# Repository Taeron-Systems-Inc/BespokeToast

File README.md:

# BespokeToast

Firmware for a toaster oven converted to a reflow soldering oven, controlled
by an Adafruit PyPortal.

This repository holds the current state of the oven: the firmware running on
it today, the measurements that firmware is built from, the runs that back
the numbers, and reference notes on the hardware it drives.

## What you need

| | |
|---|---|
| The oven | a PyPortal wired to a mains relay and an MCP9601 thermocouple amplifier (Adafruit 5165) and a type-K probe (Adafruit 3245) — `docs/hardware.md` describes the one this was built for |
| A host | anything running Python 3 that can mount USB mass storage and open a serial port. A Raspberry Pi is enough |
| A build host | only to change anything under `firmware/oven/`: ~3 GB of disk and an ARM toolchain. It does not have to be the machine attached to the oven |

## Putting the firmware on a board for the first time

The oven's own package is **frozen into the CircuitPython image**, so an
install is two halves: an image to flash, and a set of files to copy.

**1. Get an image.** Either build one — `docs/frozen-build.md` has the
toolchain, the source version and the one patch that is required — or use
an image that was built and tested earlier, if you have one. Images are not
in this repository: a `.uf2` is a build artefact, and the one that matters
is always paired with a `code.py`, which is not frozen and does not travel
inside it. Keep the pair together.

**2. Flash it.** The board must be in its UF2 bootloader, which shows up as
a volume named `PORTALBOOT`. On a board already running this firmware, ask
for it over the serial console:

```python
import microcontroller
microcontroller.on_next_reset(microcontroller.RunMode.BOOTLOADER)
microcontroller.reset()
```

On a board that will not boot, or has never run this, double-tap the reset
button instead — which on this oven means opening the panel. Copy the
`.uf2` onto `PORTALBOOT`; the board reboots itself and comes back as
`CIRCUITPY`.

**3. Copy the files that are not frozen.** Mount the volume writable and
deploy:

```
sudo mount -o rw,uid=$(id -u) /dev/disk/by-label/CIRCUITPY /mnt/circuitpy
python3 tools/deploy.py /mnt/circuitpy --dry-run    # what it would write
python3 tools/deploy.py /mnt/circuitpy
```

That copies `boot.py`, `code.py`, `settings.toml`, `profiles/` and
`assets/`, plus `data/oven-characterisation.json` as `characterisation.json`,
then verifies every file by digest. It skips `oven/` when it sees the board
is running a frozen build, refuses to run while a profile is running, and
refuses if the Adafruit libraries have reappeared on the volume — a copy
there shadows the frozen one and silently costs about 20 kB of RAM.

**4. Give it the network, if you want the web page.** Copy
`wifi.json.example` to `wifi.json` **on the volume** — not into this
repository — and fill in the SSIDs and passwords:

```
cp wifi.json.example /mnt/circuitpy/wifi.json
$EDITOR /mnt/circuitpy/wifi.json
```

The oven scans and joins whichever listed network it hears most strongly.
Without the file it runs perfectly well, with logs stamped from boot
instead of wall clock and no page. `wifi.json` is in `.gitignore`, deploy
never writes it, and anyone who can plug a cable into the board can read
it — `docs/network.md` covers that and the rest.

The template also carries two worked examples, switched off behind
underscored keys: a network entry with a **fixed address** (`ip` and
`gateway`, required together), and an **archive** block that POSTs each
finished run to a receiver — `tools/collector/serve.py` is one. Neither is
needed to use the oven.

**5. Hand the volume back to the oven.**

```
sudo umount /mnt/circuitpy
python3 tools/deploy.py --standalone
```

A deploy needs the **host** to own `CIRCUITPY`; the oven needs to own it to
record a run. Only one direction is automatic, so an oven left in host mode
runs perfectly and keeps no record of it. The power-on screen says which
mode it is in, next to *run logging*.

**6. Check it came up.** The splash and self-test panel, then the home
screen within about 15 seconds; the network line fills in behind it. Press
nothing until the home screen shows a temperature that looks like the room.

## Getting changes onto an oven that already runs it

Which path you need depends on the file:

| Changed | How it ships |
|---|---|
| `code.py`, `profiles/`, `assets/`, `characterisation.json` | `tools/deploy.py`, as above |
| anything under `firmware/oven/` | rebuild and reflash |

```
export TOASTER_BUILD_HOST=user@host    # the machine with the toolchain
python3 tools/release.py --check       # what would happen, touching nothing
python3 tools/release.py --flash       # build, flash, verify
python3 tools/release.py --rollback    # the image before the last one
```

Writing to `CIRCUITPY` triggers CircuitPython's auto-reload, which restarts
the controller immediately. Never deploy while a profile is running; deploy
refuses unless forced.

## Testing

```
python3 -m pytest tests/
python3 tools/score_runs.py      # recompute the figures the docs quote
```

Everything runs on a laptop. That is deliberate and enforced: a test parses
every module in `oven/` and fails if anything other than `hardware.py`
imports `board`. The previous firmware became untestable one import at a
time. `code.py` is never imported by the suite — it needs a board — so it
is checked by parsing instead.

`tools/onboard_test.py` is the other half: it drives the new code on a real
board from the REPL without replacing what the board boots, which is the
right first step on a board that has never run this firmware.

## Safety

This switches 120 VAC into a heating element.

The relay fails safe: `D4` has an external pulldown, so the relay is
de-energised whenever the pin is not driven — which includes every reset,
every Ctrl-C and every auto-reload. A supervisor independent of the control
loop holds a 260 C ceiling, an enclosure limit, rate and stall guards, and
ABORT is always available. The web page cannot start or abort a run, and a
test walks the routes to keep it that way.

Read `docs/hardware.md` before working on the oven, and
`docs/control-loop.md` before changing how it heats. Every run behind the
numbers in those documents was made with an **empty oven**.

## Layout

```
firmware/    What ships to the device.
  code.py    Entry point: screens, console, web service, wiring.
  oven/      Control, safety, profiles, metrics, interface. Only
             hardware.py touches the board; everything else is plain
             stdlib and runs under CPython.
  profiles/  Reflow and bake profiles as JSON.
  assets/    Fonts and logo.
tests/       pytest, off-hardware. Includes a simulated oven built from
             this oven's own measured response.
tools/       Host-side: deploy, release and rollback, profile generation,
             plant identification, run scoring, screen rendering.
  device/    Runs on the board over the serial console.
  host/      Runs on the bench machine.
  collector/ Receives finished runs.
  design/    Simulation harnesses used to choose the control loop.
data/        Measured characterisation, step tests, and the runs the
             documentation cites. See data/README.md.
docs/        Hardware, network, control loop, profiles, build, validation.
```

## Documentation

| | |
|---|---|
| `docs/hardware.md` | the oven, the controller, what is measured and what is assumed |
| `docs/control-loop.md` | how it heats, what it achieves, and the rules a replacement must keep |
| `docs/profiles.md` | each paste's profile and why its numbers are what they are |
| `docs/network.md` | credentials, the web page, what the radio costs |
| `docs/frozen-build.md` | building, flashing, rolling back, who owns the volume |
| `docs/on-device-validation.md` | what has actually been run |
| `data/README.md` | which runs are in the repository, and how to fetch one that is not |

## Tags

| | |
|---|---|
| `v1` | the oven's state as found, before the rewrite |
| `v2.0` | this firmware: pre-charge, predictive tracking, supervisor, run logging. The firmware reports the same name on the splash and in every run log header |

A tag records the source. The image and `code.py` that were tested together
are kept outside the repository, because a `.uf2` is a build artefact; see
*Rolling back* in `docs/control-loop.md`.

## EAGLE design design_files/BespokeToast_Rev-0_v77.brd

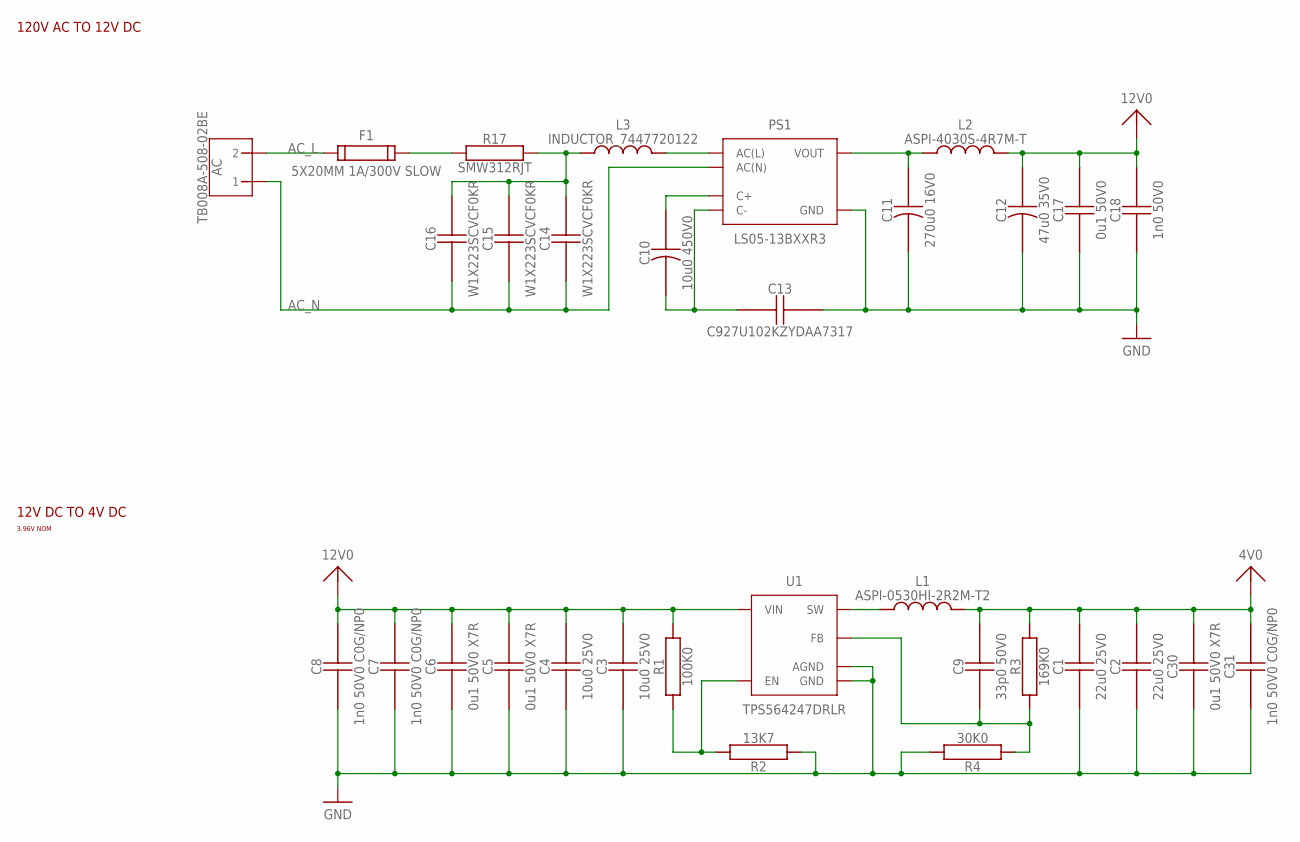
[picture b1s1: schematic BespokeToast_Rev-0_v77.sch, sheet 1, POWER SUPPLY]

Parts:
AC: TB008A-508-02BE
C1, C2: 22u0 25V0; SAMSUNG_CAP-0805
C3, C4: 10u0 25V0; SAMSUNG_CAP-0805
C5, C6, C30: 0u1 50V0 X7R; SAMSUNG_CAP-0402
C7, C8, C31: 1n0 50V0 C0G/NP0; SAMSUNG_CAP-0402
C9: 33p0 50V0; SAMSUNG_CAP-0402
C10: 10u0 450V0; RUBYCON_CAP-POL-5X10
C11: 270u0 16V0; RUBYCON_CAP-POL-3.5X8
C12: 47u0 35V0; RUBYCON_CAP-POL-3.5X8
C13: C927U102KZYDAA7317; TH_CAP-7.5
C14, C15, C16: W1X223SCVCF0KR; TH_CAP-7.5
C17: 0u1 50V0; SAMSUNG_CAP-0402
C18: 1n0 50V0; SAMSUNG_CAP-0402
F1: 5X20MM 1A/300V SLOW; FC-203-22
L1: ASPI-0530HI-2R2M-T2
L2: ASPI-4030S-4R7M-T
L3: INDUCTOR_7447720122; 7447720122
PS1: LS05-13BXXR3
R1: 100K0; YAGEO_RES-0402
R2: 13K7; YAGEO_RES-0402
R3: 169K0; YAGEO_RES-0402
R4: 30K0; YAGEO_RES-0402
R17: SMW312RJT
U1: TPS564247DRLR

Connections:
4V0: C1.P$2, C2.P$2, C9.P$2, C30.P$2, C31.P$2, L1.P$2, R3.P$2; also elsewhere on the board
12V0: C3.P$2, C4.P$2, C5.P$2, C6.P$2, C7.P$2, C8.P$2, C12.+, C17.P$2, C18.P$2, L2.P$2, R1.P$2, U1.P$1 (VIN); also elsewhere on the board
AC_L: AC.P$2 (2), F1.P$1, F1.P$2; also elsewhere on the board
AC_N: AC.P$1 (1), C14.P$1, C15.P$1, C16.P$1, PS1.P$2 (AC(N)); also elsewhere on the board
GND: C1.P$1, C2.P$1, C3.P$1, C4.P$1, C5.P$1, C6.P$1, C7.P$1, C8.P$1, C11.-, C12.-, C13.P$2, C17.P$1, C18.P$1, C30.P$1, C31.P$1, PS1.P$5 (GND), R2.P$1, R4.P$2, U1.P$3 (GND), U1.P$4 (AGND); also elsewhere on the board
unnamed: R1.P$1, R2.P$2, U1.P$5 (EN)
unnamed: C10.+, PS1.P$3 (C+)
unnamed: C10.-, C13.P$1, PS1.P$4 (C-)
unnamed: C11.+, L2.P$1, PS1.P$6 (VOUT)
unnamed: F1.P$3, F1.P$4, R17.P$2
unnamed: C9.P$1, R3.P$1, R4.P$1, U1.P$6 (FB)
unnamed: C14.P$2, C15.P$2, C16.P$2, L3.P$1, R17.P$1
unnamed: L3.P$2, PS1.P$1 (AC(L))
OUT: L1.P$1, U1.P$2 (SW)

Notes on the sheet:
120V AC TO 12V DC
12V DC TO 4V DC
3.96V NOM

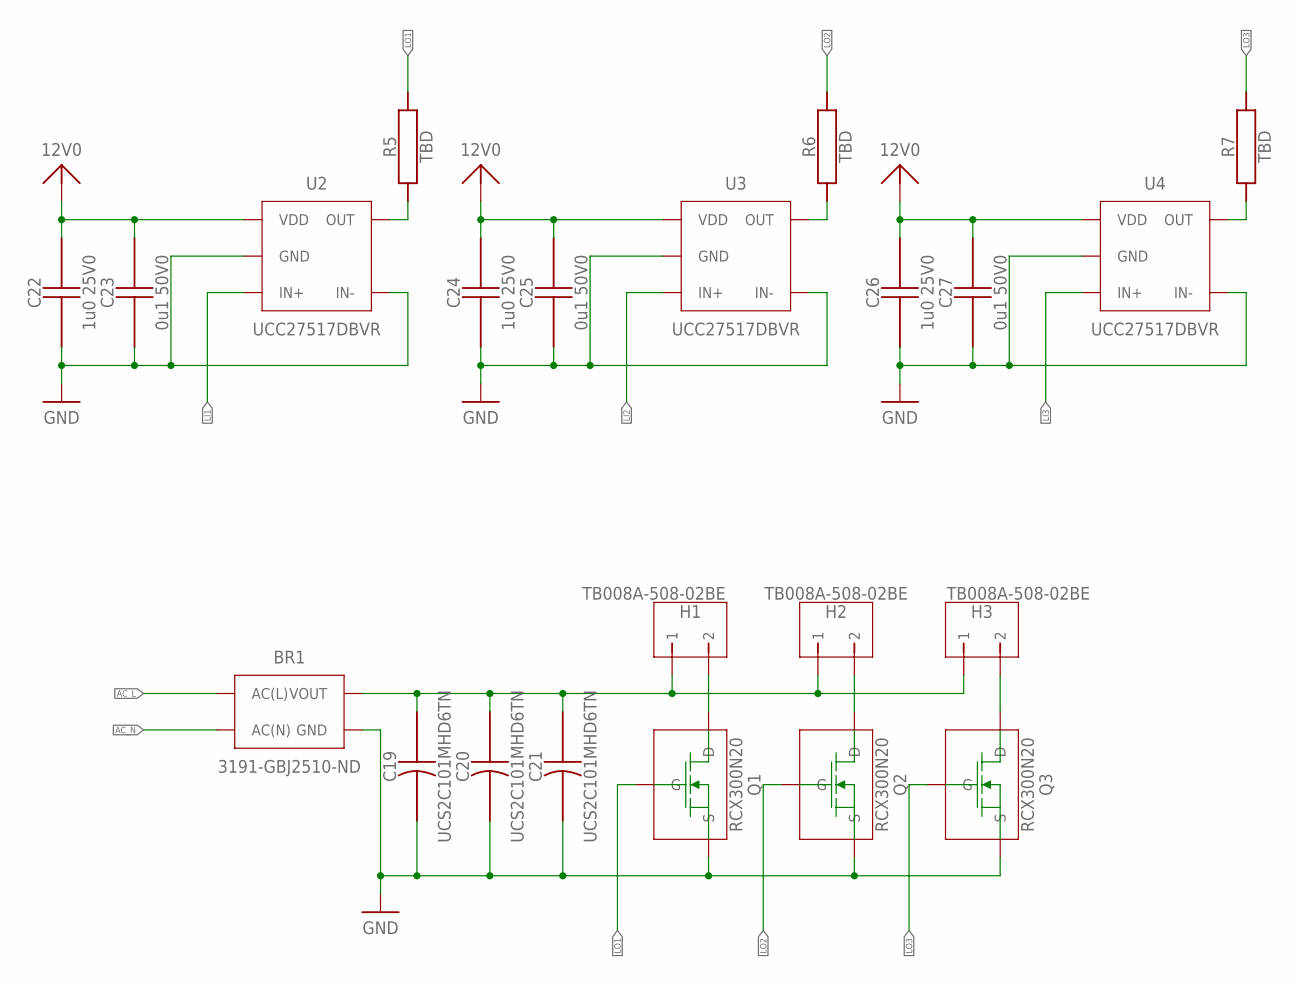
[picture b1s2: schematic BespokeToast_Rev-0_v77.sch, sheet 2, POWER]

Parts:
BR1: 3191-GBJ2510-ND; GBJ2510
C19, C20, C21: UCS2C101MHD6TN; RUBYCON_CAP-POL-7.5X16
C22, C24, C26: 1u0 25V0; SAMSUNG_CAP-0805
C23, C25, C27: 0u1 50V0; SAMSUNG_CAP-0402
H1, H2, H3: TB008A-508-02BE
Q1, Q2, Q3: RCX300N20; FET_TO220-VTH
R5, R6, R7: TBD; YAGEO_RES-0402
U2, U3, U4: UCC27517DBVR

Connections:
12V0: C22.P$2, C23.P$2, C24.P$2, C25.P$2, C26.P$2, C27.P$2, U2.P$1 (VDD), U3.P$1 (VDD), U4.P$1 (VDD); also elsewhere on the board
AC_L: BR1.P$2 (AC(L)); also elsewhere on the board
AC_N: BR1.P$3 (AC(N)); also elsewhere on the board
GND: BR1.P$4 (GND), C19.-, C20.-, C21.-, C22.P$1, C23.P$1, C24.P$1, C25.P$1, C26.P$1, C27.P$1, Q1.S, Q2.S, Q3.S, U2.P$2 (GND), U2.P$4 (IN-), U3.P$2 (GND), U3.P$4 (IN-), U4.P$2 (GND), U4.P$4 (IN-); also elsewhere on the board
LI1: U2.P$3 (IN+); also elsewhere on the board
LI2: U3.P$3 (IN+); also elsewhere on the board
LI3: U4.P$3 (IN+); also elsewhere on the board
LO1: Q1.G, R5.P$2
LO2: Q2.G, R6.P$2
LO3: Q3.G, R7.P$2
unnamed: H1.P$2 (2), Q1.D
unnamed: H2.P$2 (2), Q2.D
unnamed: H3.P$2 (2), Q3.D
unnamed: BR1.P$1 (VOUT), C19.+, C20.+, C21.+, H1.P$1 (1), H2.P$1 (1), H3.P$1 (1)
unnamed: R6.P$1, U3.P$5 (OUT)
unnamed: R5.P$1, U2.P$5 (OUT)
unnamed: R7.P$1, U4.P$5 (OUT)

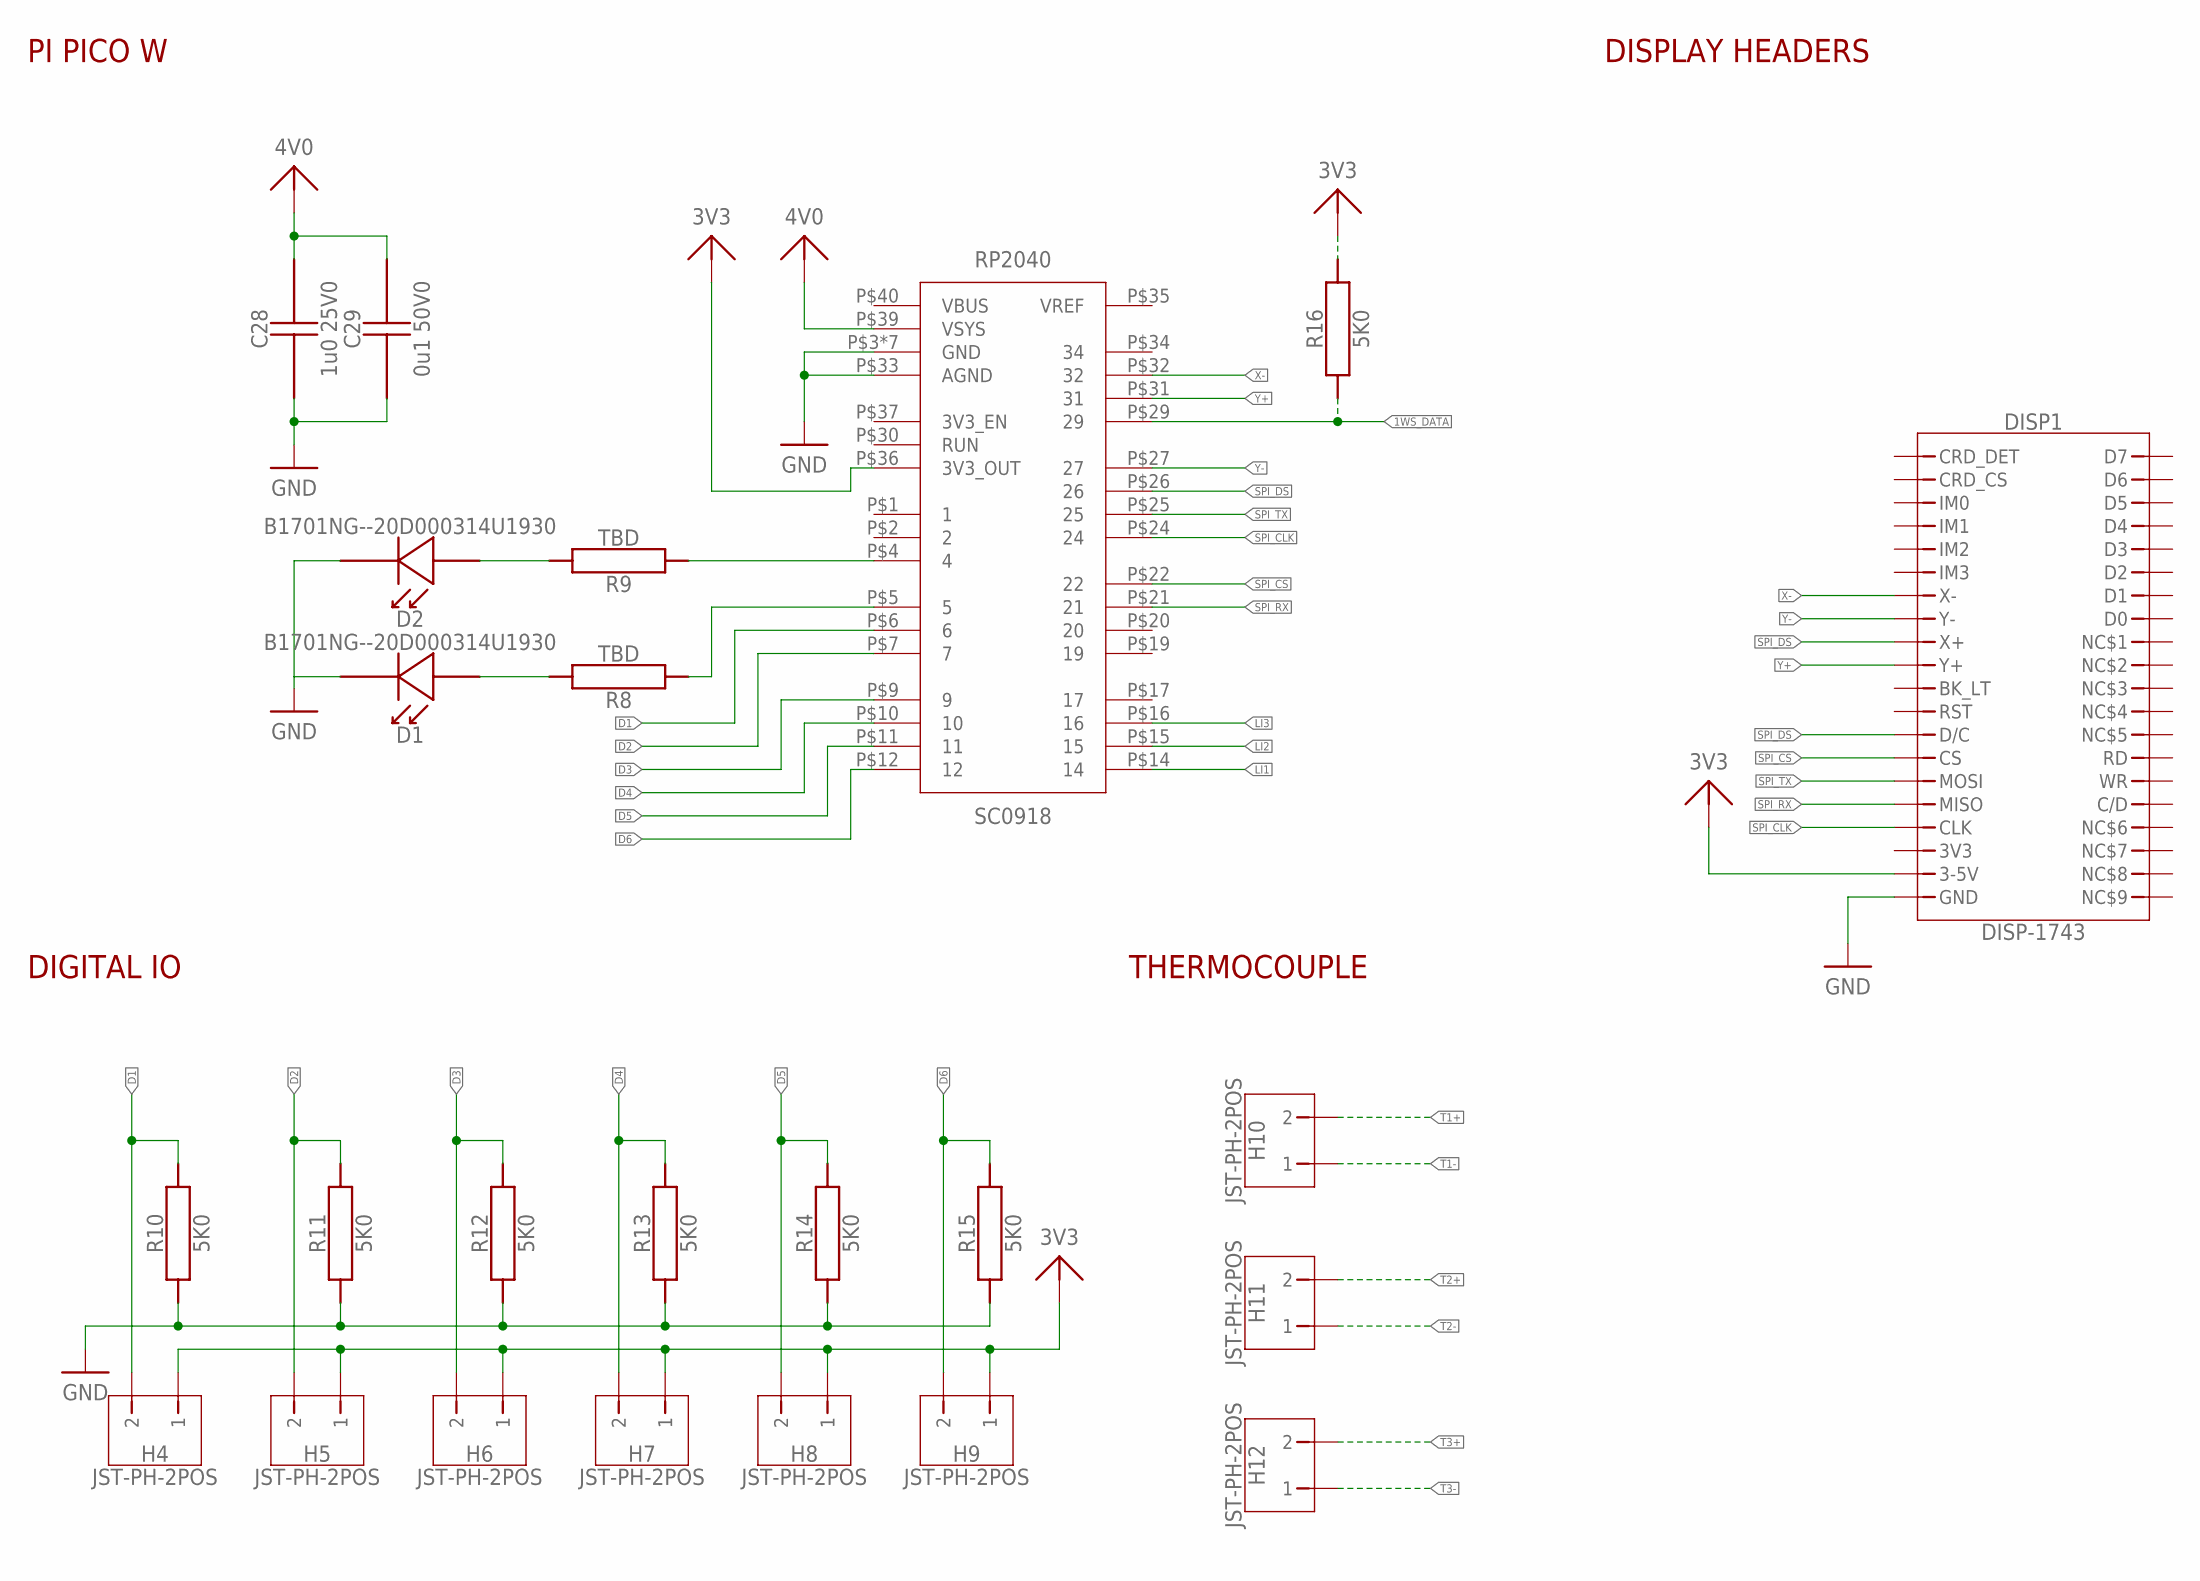
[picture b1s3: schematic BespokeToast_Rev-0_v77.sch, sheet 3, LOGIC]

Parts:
C28: 1u0 25V0; SAMSUNG_CAP-0805
C29: 0u1 50V0; SAMSUNG_CAP-0402
D1, D2: B1701NG--20D000314U1930
DISP1: DISP-1743
H4, H5, H6, H7, H8, H9, H10, H11, H12: JST-PH-2POS
R8, R9: TBD; YAGEO_RES-0402
R10, R11, R12, R13, R14, R15, R16: 5K0; YAGEO_RES-0402
RP2040: SC0918; SC0915

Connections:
1WS_DATA: R16.P$1, RP2040.P$29 (29); also elsewhere on the board
3V3: DISP1.P$19 (3-5V), H4.P$1 (1), H5.P$1 (1), H6.P$1 (1), H7.P$1 (1), H8.P$1 (1), H9.P$1 (1), R16.P$2, RP2040.P$36 (3V3_OUT)
4V0: C28.P$2, C29.P$2, RP2040.P$39 (VSYS); also elsewhere on the board
D1: H4.P$2 (2), R10.P$2, RP2040.P$6 (6)
D2: H5.P$2 (2), R11.P$2, RP2040.P$7 (7)
D3: H6.P$2 (2), R12.P$2, RP2040.P$9 (9)
D4: H7.P$2 (2), R13.P$2, RP2040.P$10 (10)
D5: H8.P$2 (2), R14.P$2, RP2040.P$11 (11)
D6: H9.P$2 (2), R15.P$2, RP2040.P$12 (12)
GND: C28.P$1, C29.P$1, D1.P$1 (VSS), D2.P$1 (VSS), DISP1.P$20 (GND), R10.P$1, R11.P$1, R12.P$1, R13.P$1, R14.P$1, R15.P$1, RP2040.P$3 (GND), RP2040.P$8 (GND), RP2040.P$13 (GND), RP2040.P$18 (GND), RP2040.P$23 (GND), RP2040.P$28 (GND), RP2040.P$33 (AGND), RP2040.P$38 (GND); also elsewhere on the board
LI1: RP2040.P$14 (14); also elsewhere on the board
LI2: RP2040.P$15 (15); also elsewhere on the board
LI3: RP2040.P$16 (16); also elsewhere on the board
unnamed: D1.P$2 (VDD), R8.P$2
unnamed: D2.P$2 (VDD), R9.P$2
unnamed: R8.P$1, RP2040.P$5 (5)
unnamed: R9.P$1, RP2040.P$4 (4)
SPI_CLK: DISP1.P$17 (CLK), RP2040.P$24 (24)
SPI_CS: DISP1.P$14 (CS), RP2040.P$22 (22)
SPI_DS: DISP1.P$9 (X+), DISP1.P$13 (D/C), RP2040.P$26 (26)
SPI_RX: DISP1.P$16 (MISO), RP2040.P$21 (21)
SPI_TX: DISP1.P$15 (MOSI), RP2040.P$25 (25)
T1+: H10.P$2 (2); also elsewhere on the board
T1-: H10.P$1 (1); also elsewhere on the board
T2+: H11.P$2 (2); also elsewhere on the board
T2-: H11.P$1 (1); also elsewhere on the board
T3+: H12.P$2 (2); also elsewhere on the board
T3-: H12.P$1 (1); also elsewhere on the board
X-: DISP1.P$7 (X-), RP2040.P$32 (32)
Y+: DISP1.P$10 (Y+), RP2040.P$31 (31)
Y-: DISP1.P$8 (Y-), RP2040.P$27 (27)

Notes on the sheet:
DIGITAL IO
PI PICO W
DISPLAY HEADERS
THERMOCOUPLE

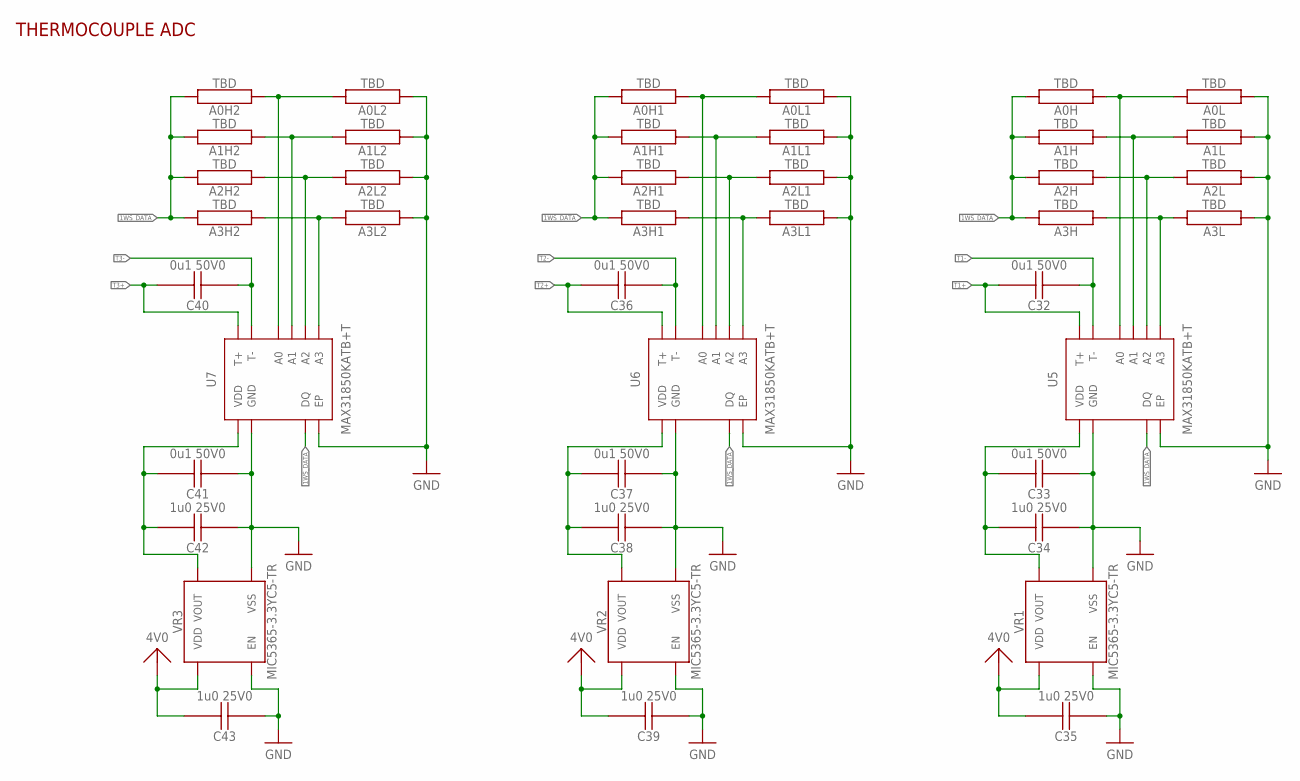
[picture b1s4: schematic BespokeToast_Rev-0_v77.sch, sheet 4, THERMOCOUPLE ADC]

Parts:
A0H, A0H1, A0H2, A0L, A0L1, A0L2, A1H, A1H1, A1H2, A1L, A1L1, A1L2, A2H, A2H1, A2H2, A2L, A2L1, A2L2, A3H, A3H1, A3H2, A3L, A3L1, A3L2: TBD; YAGEO_RES-0402
C32, C33, C36, C37, C40, C41: 0u1 50V0; SAMSUNG_CAP-0402
C34, C35, C38, C39, C42, C43: 1u0 25V0; SAMSUNG_CAP-0603
U5, U6, U7: MAX31850KATB+T; MAX31850
VR1, VR2, VR3: MIC5365-3.3YC5-TR

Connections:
1WS_DATA: A0H.P$2, A0H1.P$2, A0H2.P$2, A1H.P$2, A1H1.P$2, A1H2.P$2, A2H.P$2, A2H1.P$2, A2H2.P$2, A3H.P$2, A3H1.P$2, A3H2.P$2, U5.P$5 (DQ), U6.P$5 (DQ), U7.P$5 (DQ); also elsewhere on the board
4V0: C35.P$2, C39.P$2, C43.P$2, VR1.P$1 (VDD), VR2.P$1 (VDD), VR3.P$1 (VDD); also elsewhere on the board
GND: A0L.P$1, A0L1.P$1, A0L2.P$1, A1L.P$1, A1L1.P$1, A1L2.P$1, A2L.P$1, A2L1.P$1, A2L2.P$1, A3L.P$1, A3L1.P$1, A3L2.P$1, C33.P$1, C34.P$1, C35.P$1, C37.P$1, C38.P$1, C39.P$1, C41.P$1, C42.P$1, C43.P$1, U5.EP, U5.P$1 (GND), U6.EP, U6.P$1 (GND), U7.EP, U7.P$1 (GND), VR1.P$2 (VSS), VR1.P$3 (EN), VR2.P$2 (VSS), VR2.P$3 (EN), VR3.P$2 (VSS), VR3.P$3 (EN); also elsewhere on the board
unnamed: A0H.P$1, A0L.P$2, U5.P$6 (A0)
unnamed: A1H.P$1, A1L.P$2, U5.P$7 (A1)
unnamed: A2H.P$1, A2L.P$2, U5.P$8 (A2)
unnamed: A3H.P$1, A3L.P$2, U5.P$9 (A3)
unnamed: A0H1.P$1, A0L1.P$2, U6.P$6 (A0)
unnamed: A1H1.P$1, A1L1.P$2, U6.P$7 (A1)
unnamed: A2H1.P$1, A2L1.P$2, U6.P$8 (A2)
unnamed: A3H1.P$1, A3L1.P$2, U6.P$9 (A3)
unnamed: C33.P$2, C34.P$2, U5.P$4 (VDD), VR1.P$5 (VOUT)
unnamed: C37.P$2, C38.P$2, U6.P$4 (VDD), VR2.P$5 (VOUT)
unnamed: A0H2.P$1, A0L2.P$2, U7.P$6 (A0)
unnamed: A1H2.P$1, A1L2.P$2, U7.P$7 (A1)
unnamed: A2H2.P$1, A2L2.P$2, U7.P$8 (A2)
unnamed: A3H2.P$1, A3L2.P$2, U7.P$9 (A3)
unnamed: C41.P$2, C42.P$2, U7.P$4 (VDD), VR3.P$5 (VOUT)
T1+: C32.P$2, U5.P$3 (T+); also elsewhere on the board
T1-: C32.P$1, U5.P$2 (T-); also elsewhere on the board
T2+: C36.P$2, U6.P$3 (T+); also elsewhere on the board
T2-: C36.P$1, U6.P$2 (T-); also elsewhere on the board
T3+: C40.P$2, U7.P$3 (T+); also elsewhere on the board
T3-: C40.P$1, U7.P$2 (T-); also elsewhere on the board

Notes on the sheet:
THERMOCOUPLE ADC

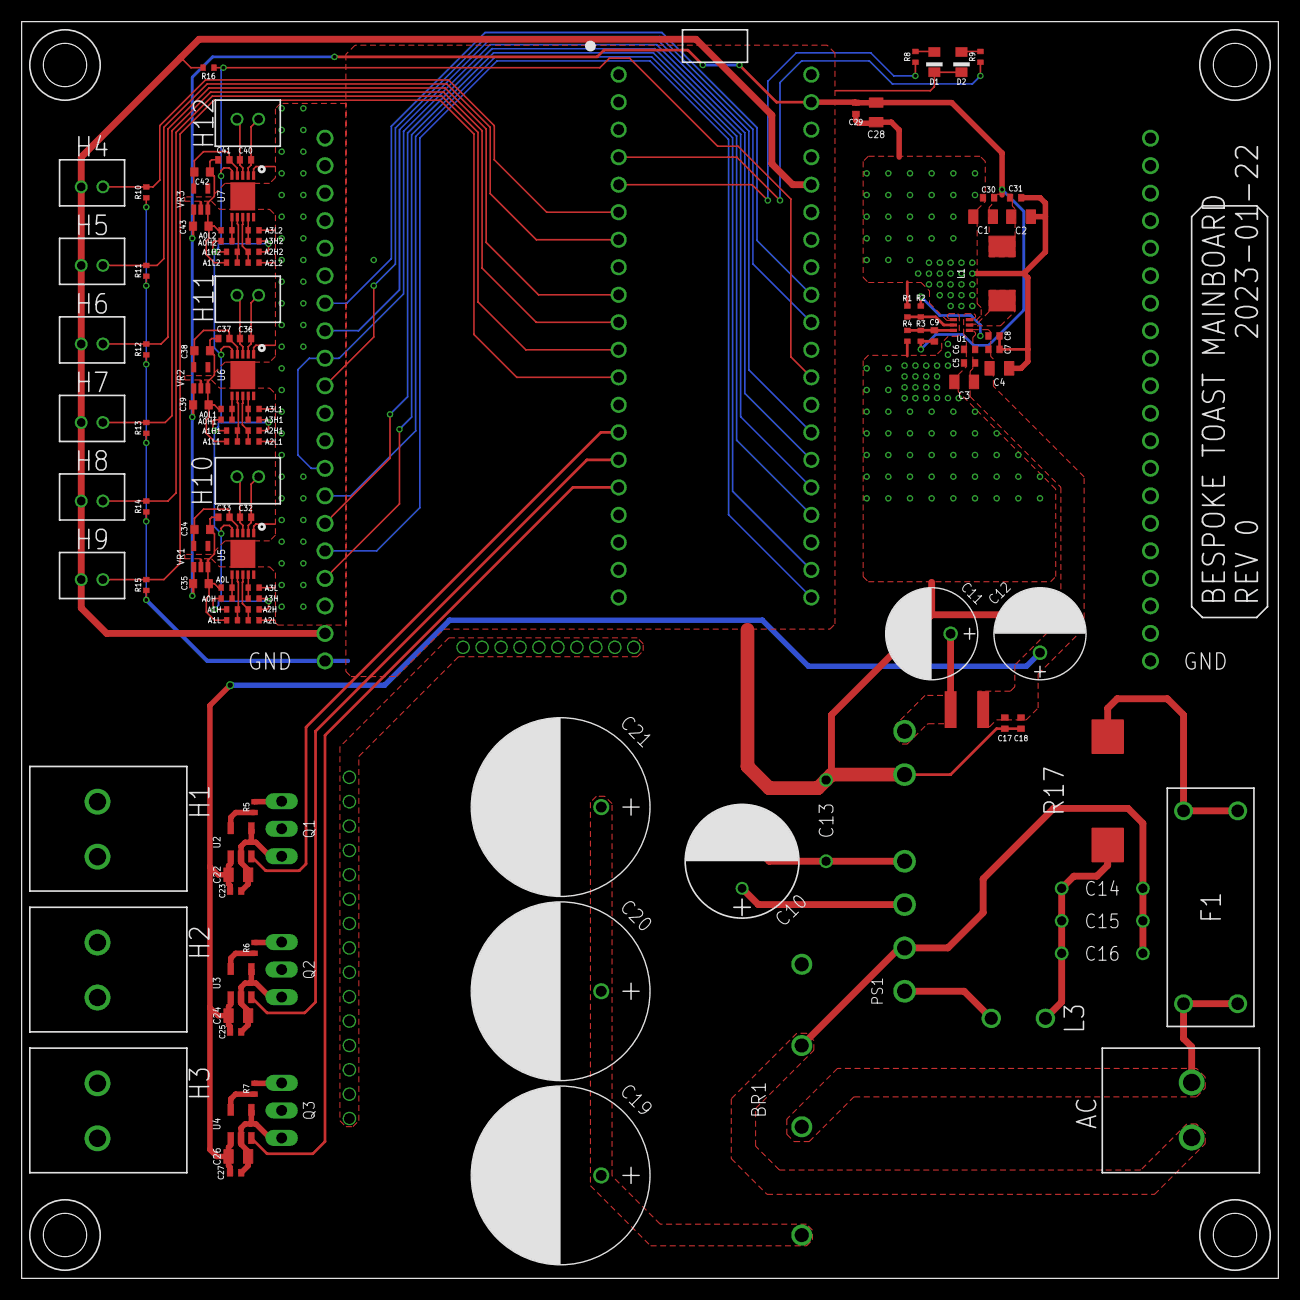
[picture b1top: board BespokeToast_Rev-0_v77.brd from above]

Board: 2 copper layers, 116.0 x 116.0 mm, 120 parts (0 on the bottom side), 68 nets.

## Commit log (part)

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2023-04-16 Delete BespokeToast_Rev-0_v77_STEP.zip
    No longer in use
2023-04-16 Delete BespokeToast_Rev-0_v77.brd
    No longer in use
2023-04-16 Delete BespokeToast_Rev-0_v77_F3D.zip
    No longer in use
2023-04-16 Delete BespokeToast_Rev-0_v77.sch
    No longer in use
2023-04-16 SAC305 Test Profile
    For testing only
2023-04-16 Update config.json
    Changed default profile
2023-10-11 Create code
